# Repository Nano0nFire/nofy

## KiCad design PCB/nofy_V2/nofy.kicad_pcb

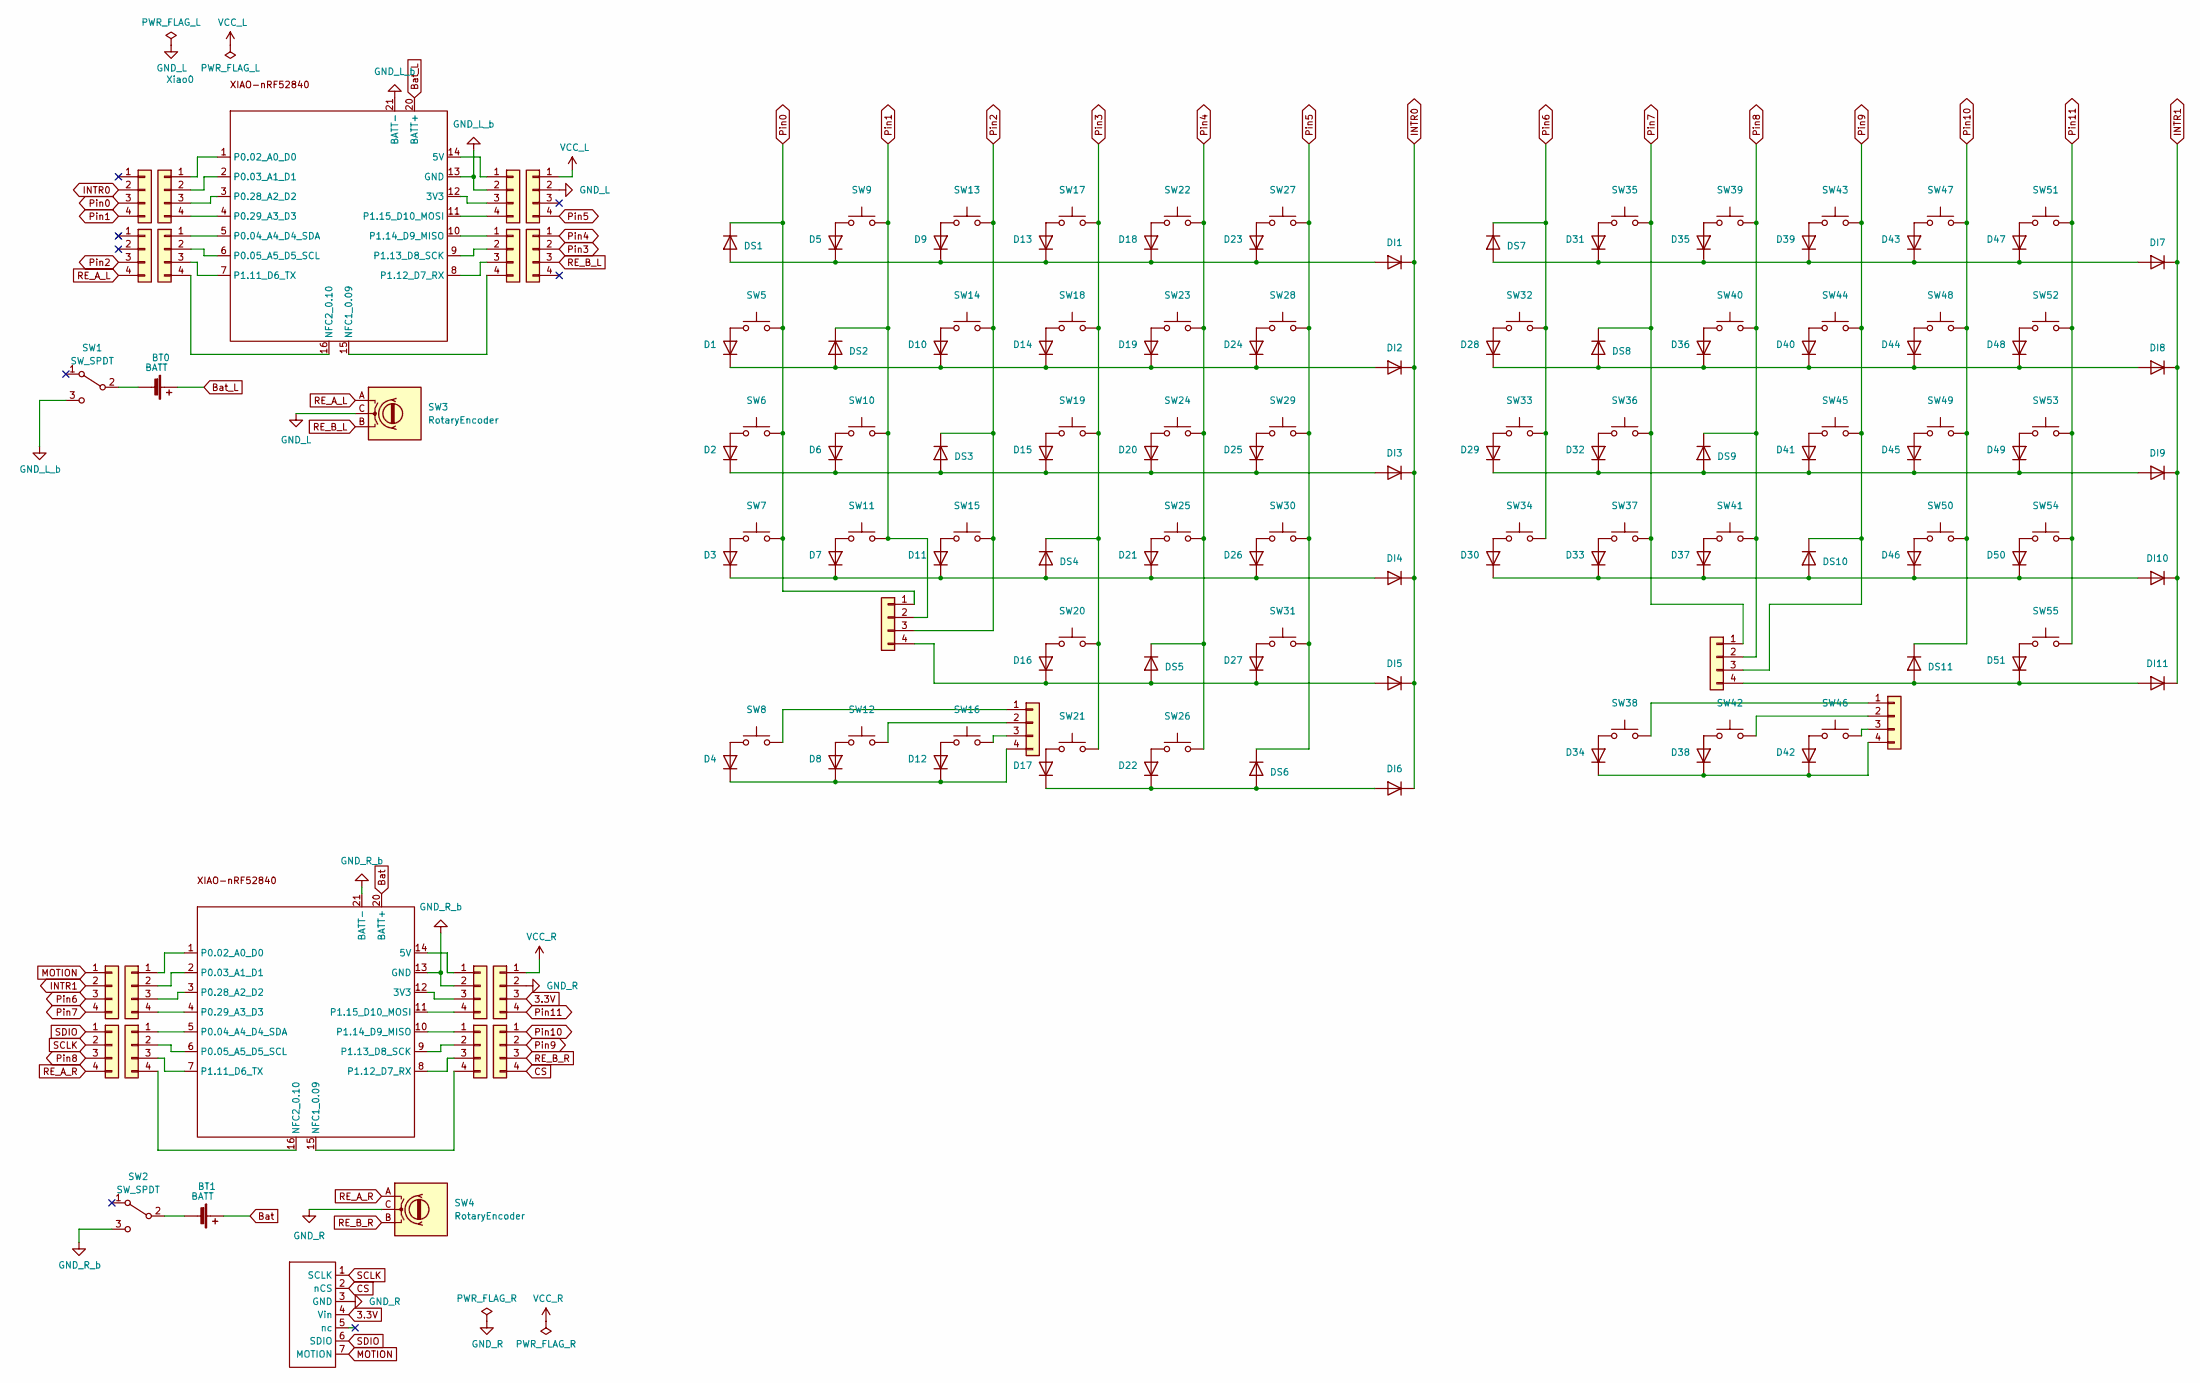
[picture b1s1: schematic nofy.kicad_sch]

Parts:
BT0, BT1: BATT; JST_S2B-PH-SM4-TB
Con_L_0, Con_L_1, Con_L_2, Con_L_3, Con_L_4, Con_L_5, Con_L_6, Con_L_7, Con_L_8, Con_L_9, Con_L_10, Con_L_11, Con_L_12, Con_L_13, Con_L_14, Con_L_15: PIn1x4; Pin1x4
D1, D2, D3, D4, D5, D6, D7, D8, D9, D10, D11, D12, D13, D14, D15, D16, D17, D18, D19, D20, D21, D22, D23, D24, D25, D26, D27, D28, D29, D30, D31, D32, D33, D34, D35, D36, D37, D38, D39, D40, D41, D42, D43, D44, D45, D46, D47, D48, D49, D50, D51: D; Diode_SMD
DI1, DI2, DI3, DI4, DI5, DI6, DI7, DI8, DI9, DI10, DI11: D; Diode_SMD
DS1, DS2, DS3, DS4, DS5, DS6, DS7, DS8, DS9, DS10, DS11: D; Diode_SMD
J9: pmw3610_connector
J18, J21, J32, J33: PIn1x4; Pin1x4
SW1, SW2: SW_SPDT; TGSW_MSK-12D19
SW3, SW4: RotaryEncoder; RotaryEncoder_EC12E
SW5, SW6, SW7, SW8, SW9, SW10, SW11, SW12, SW13, SW14, SW15, SW16, SW17, SW18, SW19, SW20, SW21, SW22, SW23, SW24, SW25, SW26, SW27, SW28, SW29, SW30, SW31, SW32, SW33, SW34, SW35, SW36, SW37, SW38, SW39, SW40, SW41, SW42, SW43, SW44, SW45, SW46, SW47, SW48, SW49, SW50, SW51, SW52, SW53, SW54, SW55: SW_PUSH; Choc_v2_Hotswap_1u_17mm
Xiao0, Xiao1: XIAO_nRF52840_wBAT_wNFC_1

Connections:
3.3V: Con_L_12.3, J9.4 (Vin)
Bat: BT1.1 (+), Xiao1.20 (BATT+)
Bat_L: BT0.1 (+), Xiao0.20 (BATT+)
CS: Con_L_14.4, J9.2 (nCS)
GND_L: Con_L_4.2, SW3.C
GND_L_b: Con_L_5.2, SW1.3 (C), Xiao0.13 (GND), Xiao0.21 (BATT-)
GND_R: Con_L_12.2, J9.3 (GND), SW4.C
GND_R_b: Con_L_13.2, SW2.3 (C), Xiao1.13 (GND), Xiao1.21 (BATT-)
INTR0: Con_L_0.2, DI1.1 (K), DI2.1 (K), DI3.1 (K), DI4.1 (K), DI5.1 (K), DI6.1 (K)
INTR1: Con_L_8.2, DI7.1 (K), DI8.1 (K), DI9.1 (K), DI10.1 (K), DI11.1 (K)
MOTION: Con_L_8.1, J9.7 (MOTION)
unnamed: BT0.2 (-), SW1.2 (B)
unnamed: BT1.2 (-), SW2.2 (B)
unnamed: Con_L_1.1, Xiao0.1 (P0.02_A0_D0)
unnamed: Con_L_1.2, Xiao0.2 (P0.03_A1_D1)
unnamed: Con_L_1.3, Xiao0.3 (P0.28_A2_D2)
unnamed: Con_L_1.4, Xiao0.4 (P0.29_A3_D3)
unnamed: Con_L_3.1, Xiao0.5 (P0.04_A4_D4_SDA)
unnamed: Con_L_3.2, Xiao0.6 (P0.05_A5_D5_SCL)
unnamed: Con_L_3.3, Xiao0.7 (P1.11_D6_TX)
unnamed: Con_L_3.4, Xiao0.16 (NFC2_0.10)
unnamed: Con_L_5.1, Xiao0.14 (5V)
unnamed: Con_L_5.3, Xiao0.12 (3V3)
unnamed: Con_L_5.4, Xiao0.11 (P1.15_D10_MOSI)
unnamed: Con_L_7.1, Xiao0.10 (P1.14_D9_MISO)
unnamed: Con_L_7.2, Xiao0.9 (P1.13_D8_SCK)
unnamed: Con_L_7.3, Xiao0.8 (P1.12_D7_RX)
unnamed: Con_L_7.4, Xiao0.15 (NFC1_0.09)
unnamed: Con_L_9.1, Xiao1.1 (P0.02_A0_D0)
unnamed: Con_L_9.2, Xiao1.2 (P0.03_A1_D1)
unnamed: Con_L_9.3, Xiao1.3 (P0.28_A2_D2)
unnamed: Con_L_9.4, Xiao1.4 (P0.29_A3_D3)
unnamed: Con_L_11.1, Xiao1.5 (P0.04_A4_D4_SDA)
unnamed: Con_L_11.2, Xiao1.6 (P0.05_A5_D5_SCL)
unnamed: Con_L_11.3, Xiao1.7 (P1.11_D6_TX)
unnamed: Con_L_11.4, Xiao1.16 (NFC2_0.10)
unnamed: Con_L_13.1, Xiao1.14 (5V)
unnamed: Con_L_13.3, Xiao1.12 (3V3)
unnamed: Con_L_13.4, Xiao1.11 (P1.15_D10_MOSI)
unnamed: Con_L_15.1, Xiao1.10 (P1.14_D9_MISO)
unnamed: Con_L_15.2, Xiao1.9 (P1.13_D8_SCK)
unnamed: Con_L_15.3, Xiao1.8 (P1.12_D7_RX)
unnamed: Con_L_15.4, Xiao1.15 (NFC1_0.09)
unnamed: D1.2 (A), SW5.2
unnamed: D1.1 (K), D10.1 (K), D14.1 (K), D19.1 (K), D24.1 (K), DI2.2 (A), DS2.2 (A)
unnamed: D2.2 (A), SW6.2
unnamed: D3.2 (A), SW7.2
unnamed: D4.2 (A), SW8.2
unnamed: D5.2 (A), SW9.2
unnamed: D6.2 (A), SW10.2
unnamed: D7.2 (A), SW11.2
unnamed: D8.2 (A), SW12.2
unnamed: D9.2 (A), SW13.2
unnamed: D10.2 (A), SW14.2
unnamed: D11.2 (A), SW15.2
unnamed: D3.1 (K), D7.1 (K), D11.1 (K), D21.1 (K), D26.1 (K), DI4.2 (A), DS4.2 (A)
unnamed: D12.2 (A), SW16.2
unnamed: D4.1 (K), D8.1 (K), D12.1 (K), J21.4
unnamed: D13.2 (A), SW17.2
unnamed: D5.1 (K), D9.1 (K), D13.1 (K), D18.1 (K), D23.1 (K), DI1.2 (A), DS1.2 (A)
unnamed: D14.2 (A), SW18.2
unnamed: D15.2 (A), SW19.2
unnamed: D2.1 (K), D6.1 (K), D15.1 (K), D20.1 (K), D25.1 (K), DI3.2 (A), DS3.2 (A)
unnamed: D16.2 (A), SW20.2
unnamed: D16.1 (K), D27.1 (K), DI5.2 (A), DS5.2 (A), J18.4
unnamed: D17.2 (A), SW21.2
unnamed: D17.1 (K), D22.1 (K), DI6.2 (A), DS6.2 (A)
unnamed: D18.2 (A), SW22.2
unnamed: D19.2 (A), SW23.2
unnamed: D20.2 (A), SW24.2
unnamed: D21.2 (A), SW25.2
unnamed: D22.2 (A), SW26.2
unnamed: D23.2 (A), SW27.2
unnamed: D24.2 (A), SW28.2
unnamed: D25.2 (A), SW29.2
unnamed: D26.2 (A), SW30.2
unnamed: D27.2 (A), SW31.2
unnamed: D28.2 (A), SW32.2
unnamed: D28.1 (K), D36.1 (K), D40.1 (K), D44.1 (K), D48.1 (K), DI8.2 (A), DS8.2 (A)
unnamed: D29.2 (A), SW33.2
unnamed: D29.1 (K), D32.1 (K), D41.1 (K), D45.1 (K), D49.1 (K), DI9.2 (A), DS9.2 (A)
unnamed: D30.2 (A), SW34.2
unnamed: D30.1 (K), D33.1 (K), D37.1 (K), D46.1 (K), D50.1 (K), DI10.2 (A), DS10.2 (A)
unnamed: D31.2 (A), SW35.2
unnamed: D31.1 (K), D35.1 (K), D39.1 (K), D43.1 (K), D47.1 (K), DI7.2 (A), DS7.2 (A)
unnamed: D32.2 (A), SW36.2
unnamed: D33.2 (A), SW37.2
unnamed: D34.2 (A), SW38.2
unnamed: D34.1 (K), D38.1 (K), D42.1 (K), J33.4
unnamed: D35.2 (A), SW39.2
unnamed: D36.2 (A), SW40.2
unnamed: D37.2 (A), SW41.2
unnamed: D38.2 (A), SW42.2
unnamed: D39.2 (A), SW43.2
unnamed: D40.2 (A), SW44.2
unnamed: D41.2 (A), SW45.2
unnamed: D42.2 (A), SW46.2
unnamed: D43.2 (A), SW47.2
unnamed: D44.2 (A), SW48.2
unnamed: D45.2 (A), SW49.2
unnamed: D46.2 (A), SW50.2
unnamed: D47.2 (A), SW51.2
unnamed: D48.2 (A), SW52.2
unnamed: D49.2 (A), SW53.2
unnamed: D50.2 (A), SW54.2
unnamed: D51.2 (A), SW55.2
unnamed: D51.1 (K), DI11.2 (A), DS11.2 (A), J32.4
unnamed: J21.1, SW8.1
unnamed: J21.2, SW12.1
unnamed: J21.3, SW16.1
unnamed: J33.1, SW38.1
unnamed: J33.2, SW42.1
unnamed: J33.3, SW46.1
Pin0: Con_L_0.3, DS1.1 (K), J18.1, SW5.1, SW6.1, SW7.1
Pin1: Con_L_0.4, DS2.1 (K), J18.2, SW9.1, SW10.1, SW11.1
Pin2: Con_L_2.3, DS3.1 (K), J18.3, SW13.1, SW14.1, SW15.1
Pin3: Con_L_6.2, DS4.1 (K), SW17.1, SW18.1, SW19.1, SW20.1, SW21.1
Pin4: Con_L_6.1, DS5.1 (K), SW22.1, SW23.1, SW24.1, SW25.1, SW26.1
Pin5: Con_L_4.4, DS6.1 (K), SW27.1, SW28.1, SW29.1, SW30.1, SW31.1
Pin6: Con_L_8.3, DS7.1 (K), SW32.1, SW33.1, SW34.1
Pin7: Con_L_8.4, DS8.1 (K), J32.1, SW35.1, SW36.1, SW37.1
Pin8: Con_L_10.3, DS9.1 (K), J32.2, SW39.1, SW40.1, SW41.1
Pin9: Con_L_14.2, DS10.1 (K), J32.3, SW43.1, SW44.1, SW45.1
Pin10: Con_L_14.1, DS11.1 (K), SW47.1, SW48.1, SW49.1, SW50.1
Pin11: Con_L_12.4, SW51.1, SW52.1, SW53.1, SW54.1, SW55.1
RE_A_L: Con_L_2.4, SW3.A
RE_A_R: Con_L_10.4, SW4.A
RE_B_L: Con_L_6.3, SW3.B
RE_B_R: Con_L_14.3, SW4.B
SCLK: Con_L_10.2, J9.1 (SCLK)
SDIO: Con_L_10.1, J9.6 (SDIO)
VCC_L: Con_L_4.1
VCC_R: Con_L_12.1

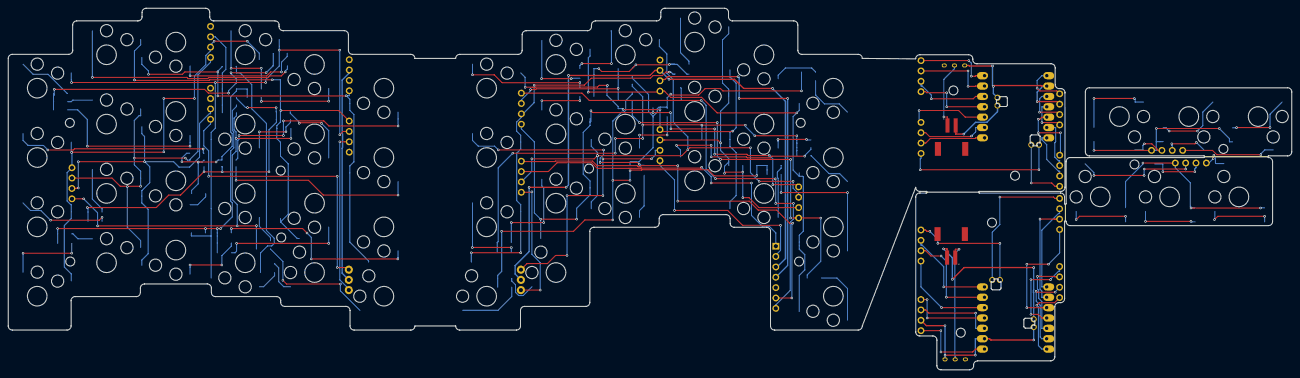
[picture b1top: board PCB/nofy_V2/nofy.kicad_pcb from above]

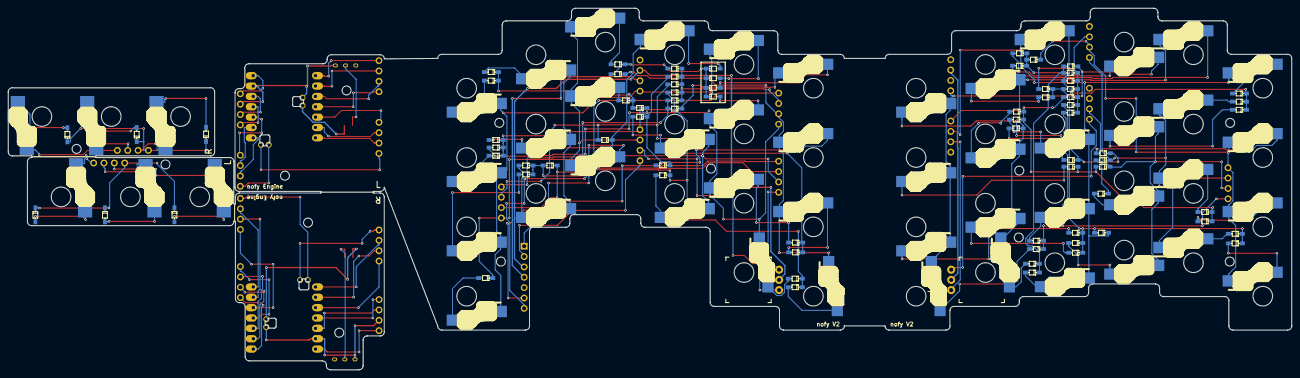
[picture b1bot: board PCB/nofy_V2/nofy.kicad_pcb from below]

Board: 2 copper layers, 314.6 x 88.6 mm, 166 parts (2 on the bottom side), 131 nets.

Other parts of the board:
Hole0, Hole1, Hole2, Hole3, Hole4, Hole5, Hole6, Hole7, Hole8, Hole9, Hole10, Hole11, Hole12: MountingHole_2.2mm_M2

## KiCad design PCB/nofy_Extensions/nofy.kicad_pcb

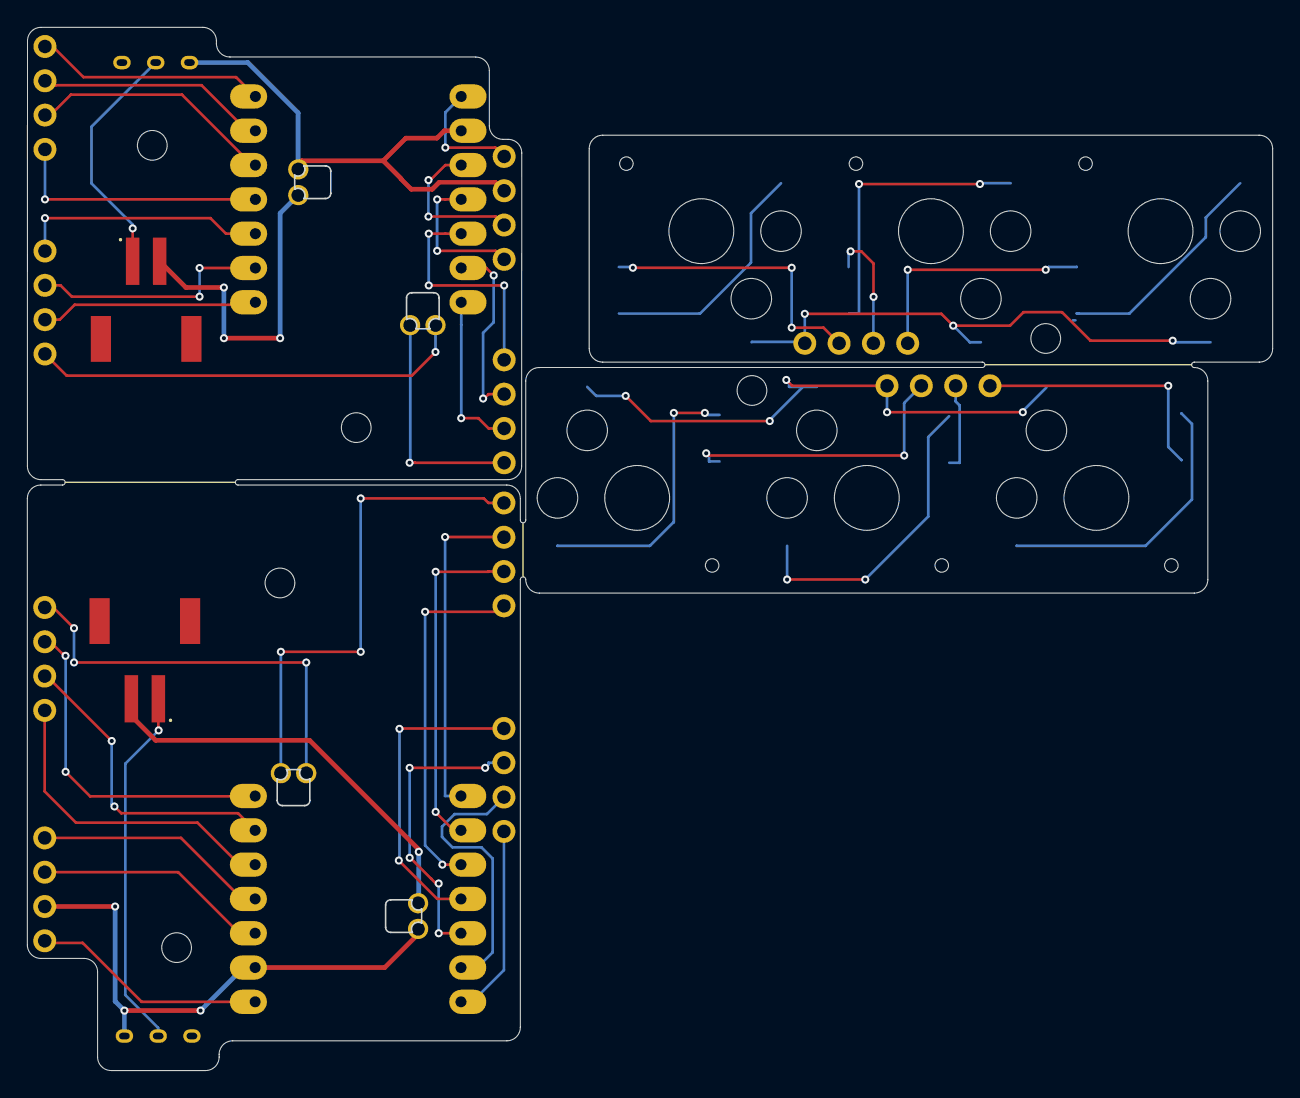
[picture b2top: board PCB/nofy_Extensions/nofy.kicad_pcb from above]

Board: 2 copper layers, 92.1 x 77.2 mm, 28 parts (0 on the bottom side), 50 nets.

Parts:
B1: BATT_L; JST_S2B-PH-SM4-TB
BT1: BATT; JST_S2B-PH-SM4-TB
D22, D23, D24, D25, D26, D27: D; Diode_SMD
J23, J24, J26, J28, J31, J33, J34, J35, J40, J41: PIn1x4; Pin1x4
SW3, SW4: SW_SPDT; TGSW_MSK-12D19
SW26, SW27, SW28, SW29, SW30, SW31: SW_PUSH; Choc_v2_Hotswap_1u_17mm
U1, U2: XIAO_nRF52840_wBAT_wNFC_1

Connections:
Bat: BT1.1 (+), U1.20 (BATT+)
Bat_L: B1.1 (+), U2.20 (BATT+)
GND_L_b: J26.2, SW3.3 (C), U2.13 (GND), U2.21 (BATT-)
GND_R_b: J34.2, SW4.3 (C), U1.13 (GND), U1.21 (BATT-)
unnamed: B1.2 (-), SW3.2 (B)
unnamed: BT1.2 (-), SW4.2 (B)
unnamed: D22.2 (A), SW26.2
unnamed: D22.1 (K), J23.2
unnamed: D23.2 (A), SW27.2
unnamed: D23.1 (K), J23.3
unnamed: D24.2 (A), SW28.2
unnamed: D24.1 (K), J23.4
unnamed: D25.2 (A), SW29.2
unnamed: D25.1 (K), J24.2
unnamed: D26.2 (A), SW30.2
unnamed: D26.1 (K), J24.3
unnamed: D27.2 (A), SW31.2
unnamed: D27.1 (K), J24.4
unnamed: J23.1, SW26.1, SW27.1, SW28.1
unnamed: J24.1, SW29.1, SW30.1, SW31.1
unnamed: J26.1, U2.14 (5V)
unnamed: J26.3, U2.12 (3V3)
unnamed: J26.4, U2.11 (P1.15_D10_MOSI)
unnamed: J28.1, U2.10 (P1.14_D9_MISO)
unnamed: J28.2, U2.9 (P1.13_D8_SCK)
unnamed: J28.3, U2.8 (P1.12_D7_RX)
unnamed: J28.4, U2.15 (NFC1_0.09)
unnamed: J31.1, U2.1 (P0.02_A0_D0)
unnamed: J31.2, U2.2 (P0.03_A1_D1)
unnamed: J31.3, U2.3 (P0.28_A2_D2)
unnamed: J31.4, U2.4 (P0.29_A3_D3)
unnamed: J33.1, U2.5 (P0.04_A4_D4_SDA)
unnamed: J33.2, U2.6 (P0.05_A5_D5_SCL)
unnamed: J33.3, U2.7 (P1.11_D6_TX)
unnamed: J33.4, U2.16 (NFC2_0.10)
unnamed: J34.1, U1.14 (5V)
unnamed: J34.3, U1.12 (3V3)
unnamed: J34.4, U1.11 (P1.15_D10_MOSI)
unnamed: J35.1, U1.10 (P1.14_D9_MISO)
unnamed: J35.2, U1.9 (P1.13_D8_SCK)
unnamed: J35.3, U1.8 (P1.12_D7_RX)
unnamed: J35.4, U1.15 (NFC1_0.09)
unnamed: J40.1, U1.1 (P0.02_A0_D0)
unnamed: J40.2, U1.2 (P0.03_A1_D1)
unnamed: J40.3, U1.3 (P0.28_A2_D2)
unnamed: J40.4, U1.4 (P0.29_A3_D3)
unnamed: J41.1, U1.5 (P0.04_A4_D4_SDA)
unnamed: J41.2, U1.6 (P0.05_A5_D5_SCL)
unnamed: J41.3, U1.7 (P1.11_D6_TX)
unnamed: J41.4, U1.16 (NFC2_0.10)

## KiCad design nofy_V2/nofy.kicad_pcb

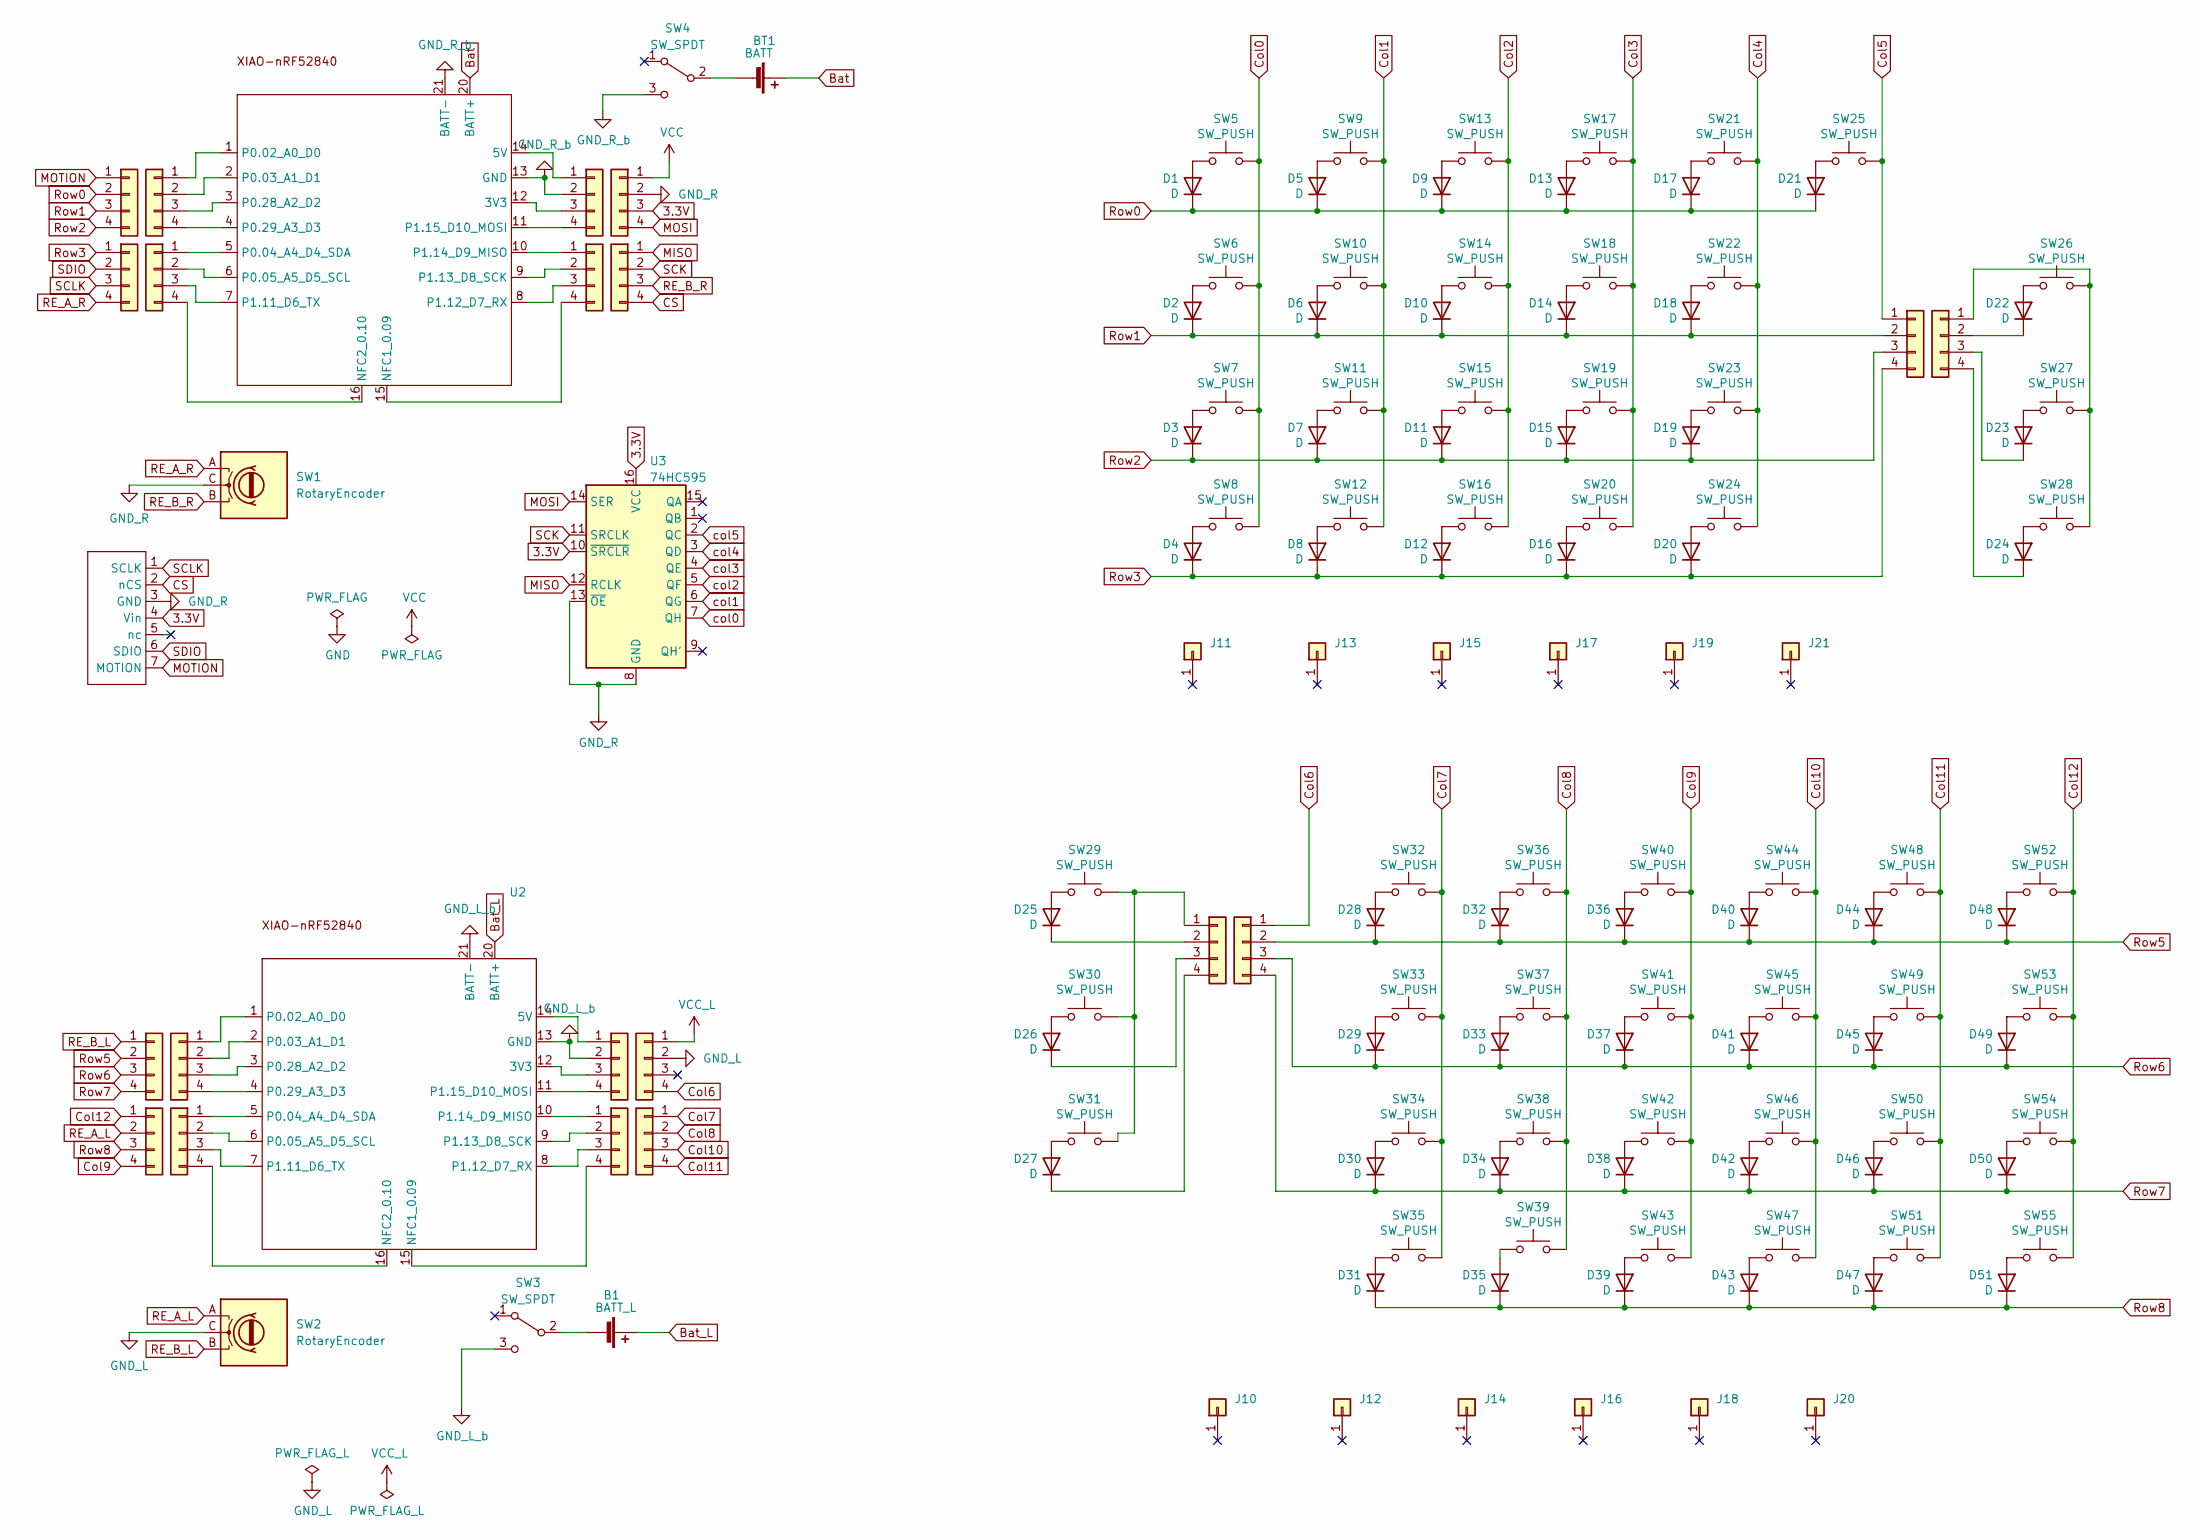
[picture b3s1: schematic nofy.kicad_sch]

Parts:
B1: BATT_L; JST_S2B-PH-SM4-TB
BT1: BATT; JST_S2B-PH-SM4-TB
D1, D2, D3, D4, D5, D6, D7, D8, D9, D10, D11, D12, D13, D14, D15, D16, D17, D18, D19, D20, D21, D22, D23, D24, D25, D26, D27, D28, D29, D30, D31, D32, D33, D34, D35, D36, D37, D38, D39, D40, D41, D42, D43, D44, D45, D46, D47, D48, D49, D50, D51: D; Diode_SMD
J2: pmw3610_connector
J10, J11, J12, J13, J14, J15, J16, J17, J18, J19, J20, J21: Conn_01x01-Connector_Generic; MountingHole_3.2mm_M3
J22, J23, J24, J25, J26, J27, J28, J29, J30, J31, J32, J33, J34, J35, J36, J37, J38, J39, J40, J41: PIn1x4; Pin1x4
SW1, SW2: RotaryEncoder; RotaryEncoder_EC12E
SW3, SW4: SW_SPDT; TGSW_MSK-12D19
SW5, SW6, SW7, SW8, SW9, SW10, SW11, SW12, SW13, SW14, SW15, SW16, SW17, SW18, SW19, SW20, SW21, SW22, SW23, SW24, SW25, SW26, SW27, SW28, SW29, SW30, SW31, SW32, SW33, SW34, SW35, SW36, SW37, SW38, SW39, SW40, SW41, SW42, SW43, SW44, SW45, SW46, SW47, SW48, SW49, SW50, SW51, SW52, SW53, SW54, SW55: SW_PUSH; Choc_v2_Hotswap_1u_17mm
U1, U2: XIAO_nRF52840_wBAT_wNFC_1
U3: 74HC595; SOIC-16_3.9x9.9mm_P1.27mm; LCSC Part Number C10092

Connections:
3.3V: J2.4 (Vin), J38.3, U3.10 (~SRCLR), U3.16 (VCC)
Bat: BT1.1 (+), U1.20 (BATT+)
Bat_L: B1.1 (+), U2.20 (BATT+)
CS: J2.2 (nCS), J39.4
Col0: SW5.1, SW6.1, SW7.1, SW8.1, U3.7 (QH)
Col1: SW9.1, SW10.1, SW11.1, SW12.1, U3.6 (QG)
Col2: SW13.1, SW14.1, SW15.1, SW16.1, U3.5 (QF)
Col3: SW17.1, SW18.1, SW19.1, SW20.1, U3.4 (QE)
Col4: SW21.1, SW22.1, SW23.1, SW24.1, U3.3 (QD)
Col5: J22.1, SW25.1, U3.2 (QC)
Col6: J25.1, J27.4
Col7: J29.1, SW32.1, SW33.1, SW34.1, SW35.1
Col8: J29.2, SW36.1, SW37.1, SW38.1, SW39.1
Col9: J32.4, SW40.1, SW41.1, SW42.1, SW43.1
Col10: J29.3, SW44.1, SW45.1, SW46.1, SW47.1
Col11: J29.4, SW48.1, SW49.1, SW50.1, SW51.1
Col12: J32.1, SW52.1, SW53.1, SW54.1, SW55.1
GND_L: J27.2, SW2.C
GND_L_b: J26.2, SW3.3 (C), U2.13 (GND), U2.21 (BATT-)
GND_R: J2.3 (GND), J38.2, SW1.C, U3.8 (GND), U3.13 (~OE)
GND_R_b: J34.2, SW4.3 (C), U1.13 (GND), U1.21 (BATT-)
MISO: J39.1, U3.12 (RCLK)
MOSI: J38.4, U3.14 (SER)
MOTION: J2.7 (MOTION), J36.1
unnamed: B1.2 (-), SW3.2 (B)
unnamed: BT1.2 (-), SW4.2 (B)
unnamed: D1.2 (A), SW5.2
unnamed: D2.2 (A), SW6.2
unnamed: D3.2 (A), SW7.2
unnamed: D4.2 (A), SW8.2
unnamed: D5.2 (A), SW9.2
unnamed: D6.2 (A), SW10.2
unnamed: D7.2 (A), SW11.2
unnamed: D8.2 (A), SW12.2
unnamed: D9.2 (A), SW13.2
unnamed: D10.2 (A), SW14.2
unnamed: D11.2 (A), SW15.2
unnamed: D12.2 (A), SW16.2
unnamed: D13.2 (A), SW17.2
unnamed: D14.2 (A), SW18.2
unnamed: D15.2 (A), SW19.2
unnamed: D16.2 (A), SW20.2
unnamed: D17.2 (A), SW21.2
unnamed: D18.2 (A), SW22.2
unnamed: D19.2 (A), SW23.2
unnamed: D20.2 (A), SW24.2
unnamed: D21.2 (A), SW25.2
unnamed: D22.2 (A), SW26.2
unnamed: D22.1 (K), J23.2
unnamed: D23.2 (A), SW27.2
unnamed: D23.1 (K), J23.3
unnamed: D24.2 (A), SW28.2
unnamed: D24.1 (K), J23.4
unnamed: D25.2 (A), SW29.2
unnamed: D25.1 (K), J24.2
unnamed: D26.2 (A), SW30.2
unnamed: D26.1 (K), J24.3
unnamed: D27.2 (A), SW31.2
unnamed: D27.1 (K), J24.4
unnamed: D28.2 (A), SW32.2
unnamed: D29.2 (A), SW33.2
unnamed: D30.2 (A), SW34.2
unnamed: D31.2 (A), SW35.2
unnamed: D32.2 (A), SW36.2
unnamed: D33.2 (A), SW37.2
unnamed: D34.2 (A), SW38.2
unnamed: D35.2 (A), SW39.2
unnamed: D36.2 (A), SW40.2
unnamed: D37.2 (A), SW41.2
unnamed: D38.2 (A), SW42.2
unnamed: D39.2 (A), SW43.2
unnamed: D40.2 (A), SW44.2
unnamed: D41.2 (A), SW45.2
unnamed: D42.2 (A), SW46.2
unnamed: D43.2 (A), SW47.2
unnamed: D44.2 (A), SW48.2
unnamed: D45.2 (A), SW49.2
unnamed: D46.2 (A), SW50.2
unnamed: D47.2 (A), SW51.2
unnamed: D48.2 (A), SW52.2
unnamed: D49.2 (A), SW53.2
unnamed: D50.2 (A), SW54.2
unnamed: D51.2 (A), SW55.2
unnamed: J23.1, SW26.1, SW27.1, SW28.1
unnamed: J24.1, SW29.1, SW30.1, SW31.1
unnamed: J26.1, U2.14 (5V)
unnamed: J26.3, U2.12 (3V3)
unnamed: J26.4, U2.11 (P1.15_D10_MOSI)
unnamed: J28.1, U2.10 (P1.14_D9_MISO)
unnamed: J28.2, U2.9 (P1.13_D8_SCK)
unnamed: J28.3, U2.8 (P1.12_D7_RX)
unnamed: J28.4, U2.15 (NFC1_0.09)
unnamed: J31.1, U2.1 (P0.02_A0_D0)
unnamed: J31.2, U2.2 (P0.03_A1_D1)
unnamed: J31.3, U2.3 (P0.28_A2_D2)
unnamed: J31.4, U2.4 (P0.29_A3_D3)
unnamed: J33.1, U2.5 (P0.04_A4_D4_SDA)
unnamed: J33.2, U2.6 (P0.05_A5_D5_SCL)
unnamed: J33.3, U2.7 (P1.11_D6_TX)
unnamed: J33.4, U2.16 (NFC2_0.10)
unnamed: J34.1, U1.14 (5V)
unnamed: J34.3, U1.12 (3V3)
unnamed: J34.4, U1.11 (P1.15_D10_MOSI)
unnamed: J35.1, U1.10 (P1.14_D9_MISO)
unnamed: J35.2, U1.9 (P1.13_D8_SCK)
unnamed: J35.3, U1.8 (P1.12_D7_RX)
unnamed: J35.4, U1.15 (NFC1_0.09)
unnamed: J40.1, U1.1 (P0.02_A0_D0)
unnamed: J40.2, U1.2 (P0.03_A1_D1)
unnamed: J40.3, U1.3 (P0.28_A2_D2)
unnamed: J40.4, U1.4 (P0.29_A3_D3)
unnamed: J41.1, U1.5 (P0.04_A4_D4_SDA)
unnamed: J41.2, U1.6 (P0.05_A5_D5_SCL)
unnamed: J41.3, U1.7 (P1.11_D6_TX)
unnamed: J41.4, U1.16 (NFC2_0.10)
RE_A_L: J32.2, SW2.A
RE_A_R: J37.4, SW1.A
RE_B_L: J30.1, SW2.B
RE_B_R: J39.3, SW1.B
Row0: D1.1 (K), D5.1 (K), D9.1 (K), D13.1 (K), D17.1 (K), D21.1 (K), J36.2
Row1: D2.1 (K), D6.1 (K), D10.1 (K), D14.1 (K), D18.1 (K), J22.2, J36.3
Row2: D3.1 (K), D7.1 (K), D11.1 (K), D15.1 (K), D19.1 (K), J22.3, J36.4
Row3: D4.1 (K), D8.1 (K), D12.1 (K), D16.1 (K), D20.1 (K), J22.4, J37.1
Row5: D28.1 (K), D32.1 (K), D36.1 (K), D40.1 (K), D44.1 (K), D48.1 (K), J25.2, J30.2
Row6: D29.1 (K), D33.1 (K), D37.1 (K), D41.1 (K), D45.1 (K), D49.1 (K), J25.3, J30.3
Row7: D30.1 (K), D34.1 (K), D38.1 (K), D42.1 (K), D46.1 (K), D50.1 (K), J25.4, J30.4
Row8: D31.1 (K), D35.1 (K), D39.1 (K), D43.1 (K), D47.1 (K), D51.1 (K), J32.3
SCK: J39.2, U3.11 (SRCLK)
SCLK: J2.1 (SCLK), J37.3
SDIO: J2.6 (SDIO), J37.2
VCC: J38.1
VCC_L: J27.1

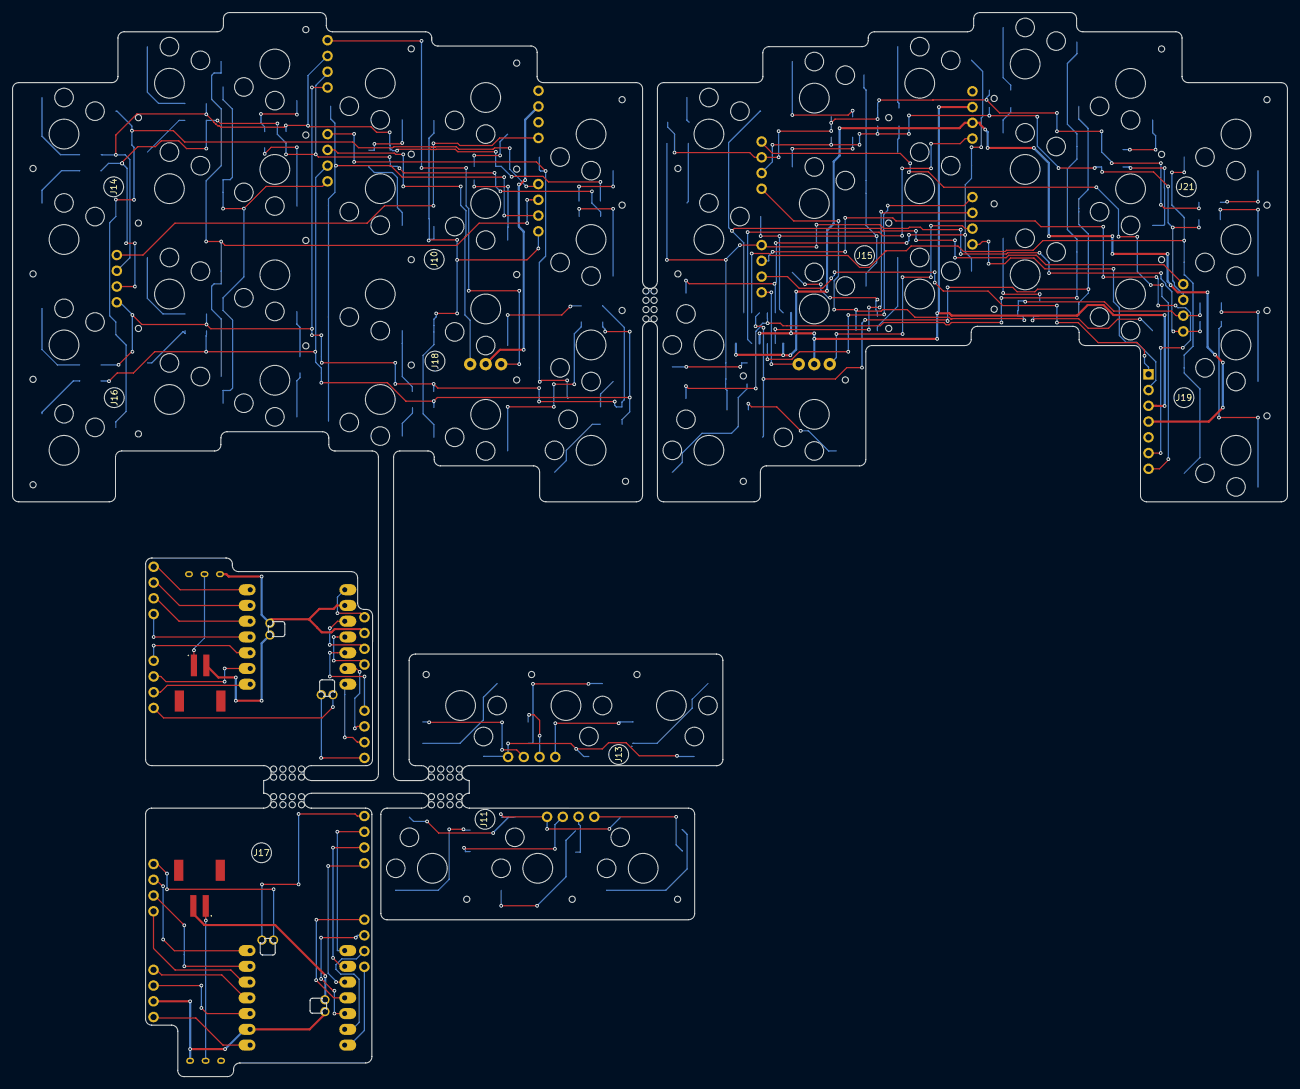
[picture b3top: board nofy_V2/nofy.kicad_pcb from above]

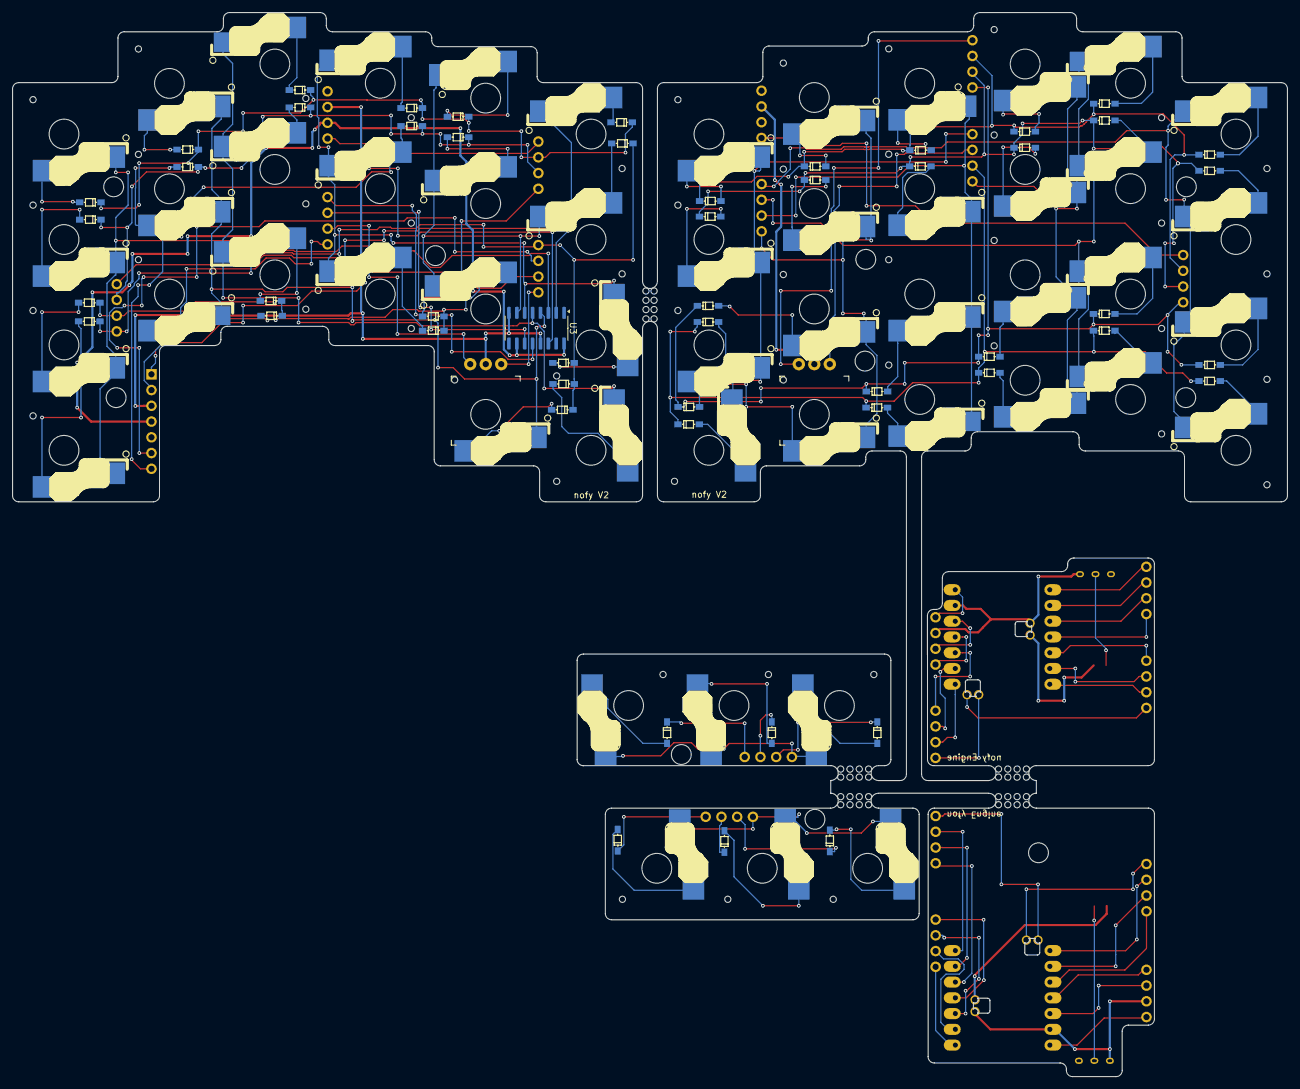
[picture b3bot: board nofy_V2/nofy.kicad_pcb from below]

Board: 2 copper layers, 205.5 x 171.5 mm, 142 parts (3 on the bottom side), 130 nets.

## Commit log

2025-03-19 Add : PCB
2025-03-19 Add : Library
2025-03-19 Update : PCB
